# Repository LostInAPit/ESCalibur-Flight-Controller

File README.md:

# ESCalibur-Flight-Controller
A flight computer for university level high power rocketry

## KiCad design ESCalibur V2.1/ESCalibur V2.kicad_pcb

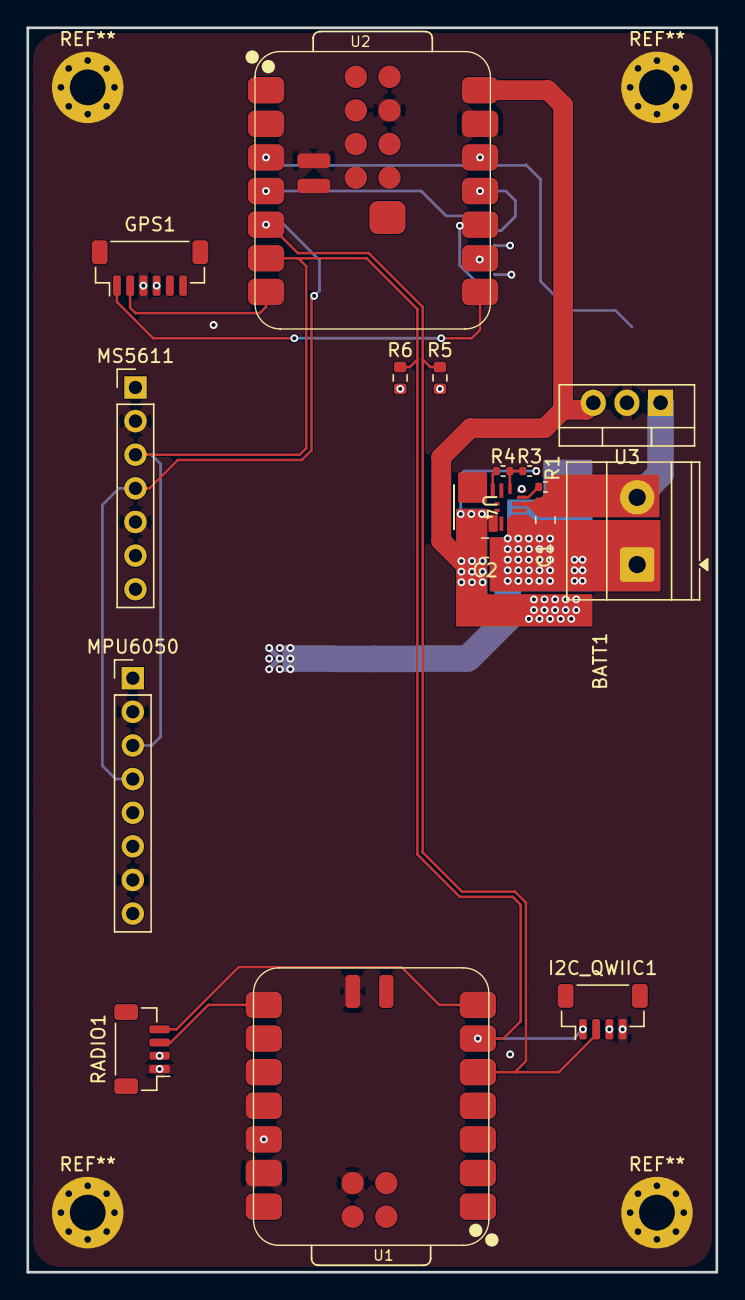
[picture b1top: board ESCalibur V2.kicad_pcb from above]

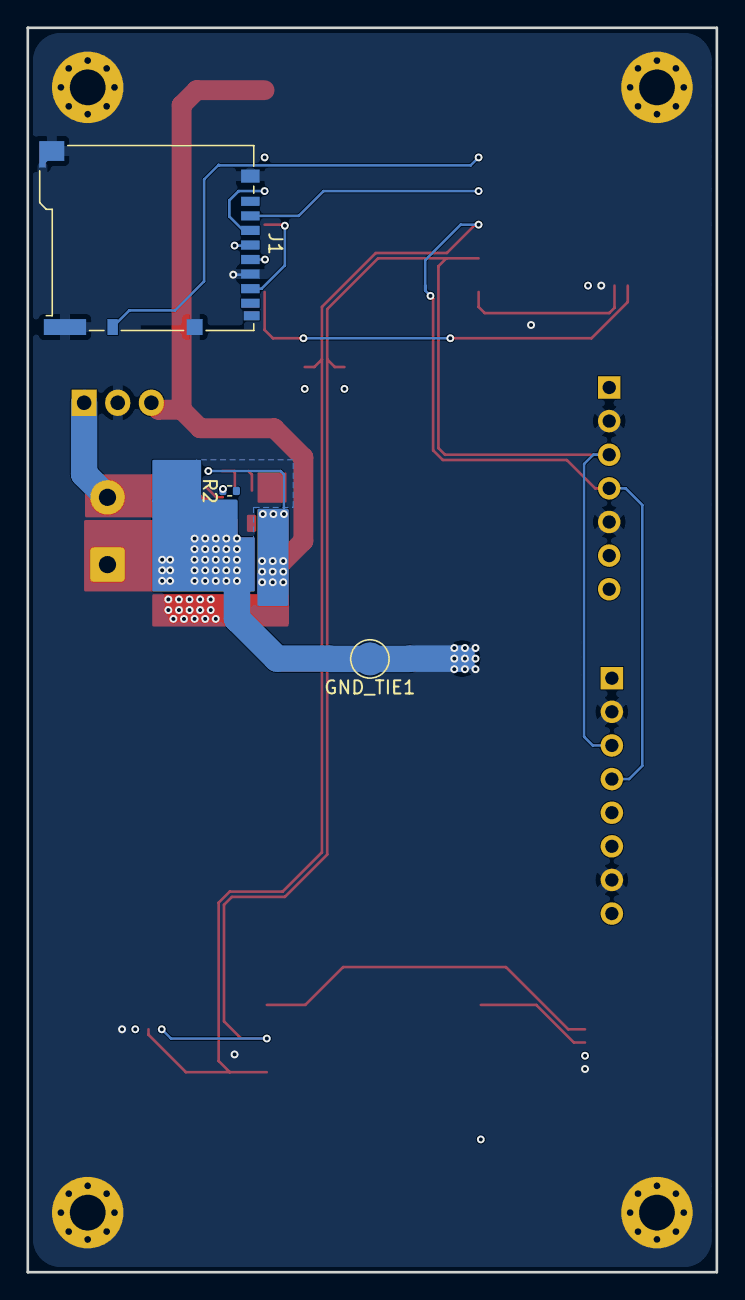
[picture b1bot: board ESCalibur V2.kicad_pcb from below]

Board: 4 copper layers, 52.1 x 94.0 mm, 22 parts (5 on the bottom side), 21 nets.

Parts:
BATT1: Conn_01x02_Socket; TerminalBlock_Phoenix_MKDS-1,5-2-5.08_1x02_P5.08mm_Horizont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
C1: 10uF; C_0805_2012Metric
C2: 22uF; C_0805_2012Metric
GND_TIE1: Conn_01x01_Pin; TestPoint_Pad_D2.5mm
GPS1: Conn_01x06_Socket; JST_SH_BM06B-SRSS-TB_1x06-1MP_P1.00mm_Vertical
I2C_QWIIC1: Conn_01x04_Socket; JST_SH_BM04B-SRSS-TB_1x04-1MP_P1.00mm_Vertical
J1: Micro_SD_Card_Det_Hirose_DM3AT; microSD_HC_Hirose_DM3BT-DSF-PEJS
JP1, JP2: NET TIE; NetTie-2_SMD_Pad2.0mm
MPU6050: Conn_01x08_Socket; PinHeader_1x08_P2.54mm_Vertical
MS5611: Conn_01x07_Socket; PinHeader_1x07_P2.54mm_Vertical
R1, R3: 100K; R_0402_1005Metric
R2: 53.6K; R_0402_1005Metric
R4: 19.1K; R_0402_1005Metric
R5, R6: 4.7K; R_0603_1608Metric
RADIO1: Conn_01x04_Socket; JST_SH_BM04B-SRSS-TB_1x04-1MP_P1.00mm_Vertical
U1: XIAO-SAMD21-SMD
U2: XIAO-ESP32-S3-SMD
U3: L7805; TO-220-3_Vertical
U4: MPM3610GQV-P; QFN3p0x5p0x1p6_MPM3610_MNP

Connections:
+3V3_MAIN: GPS1.4, I2C_QWIIC1.3, J1.4 (VDD), MPU6050.1, MS5611.1, R5.1, R6.1, RADIO1.2, U1.12 (3V3_OUT), U2.12 (3V3_OUT)
+5V: C2.1, R3.2, U2.14 (VBUS), U3.3 (OUT), U4.7 (OUT), U4.8 (OUT), U4.9 (OUT)
+BATT: BATT1.2, C1.1, R1.2, U3.1 (IN), U4.16 (IN)
CD: J1.10 (DET_A), U2.3 (D2)
CLK: J1.5 (CLK), U2.9 (D8)
CS: J1.2 (DAT3/CD), U2.4 (D3)
DI: J1.3 (CMD), U2.11 (D10)
DO: J1.7 (DAT0), U2.10 (D9)
GND: GPS1.3, I2C_QWIIC1.4, J1.6 (VSS), J1.SH (SHIELD), JP1.1 (A), MPU6050.2, MPU6050.7, MS5611.2, MS5611.5, RADIO1.1, U1.13 (GND), U1.18 (GND), U1.20 (GND), U2.13 (GND), U2.18 (GND), U2.24 (GND), U3.2 (GND)
GNDA: R2.2, R4.1, U4.3 (AGND)
GNDPWR: BATT1.1, C1.2, C2.2, JP2.2 (B), U4.12 (PGND), U4.13 (PGND), U4.14 (PGND)
GPS_RX: GPS1.2, U2.7 (D6)
GPS_TX: GPS1.1, U2.8 (D7)
unnamed: GND_TIE1.1 (Pin_1_1), JP1.2 (B), JP2.1 (A)
unnamed: R2.1, U4.18 (AAM)
unnamed: R3.1, R4.2, U4.1 (FB)
PWR_EN: R1.1, U4.17 (EN)
RADIO_RX: RADIO1.4, U1.7 (D6)
RADIO_TX: RADIO1.3, U1.8 (D7)
SCL: I2C_QWIIC1.1, MPU6050.3, MS5611.3, R6.2, U1.6 (D5), U2.6 (D5)
SDA: I2C_QWIIC1.2, MPU6050.4, MS5611.4, R5.2, U1.5 (D4), U2.5 (D4)
